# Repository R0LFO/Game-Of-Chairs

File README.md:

# Game-Of-Chairs
ECE 362 miniproject

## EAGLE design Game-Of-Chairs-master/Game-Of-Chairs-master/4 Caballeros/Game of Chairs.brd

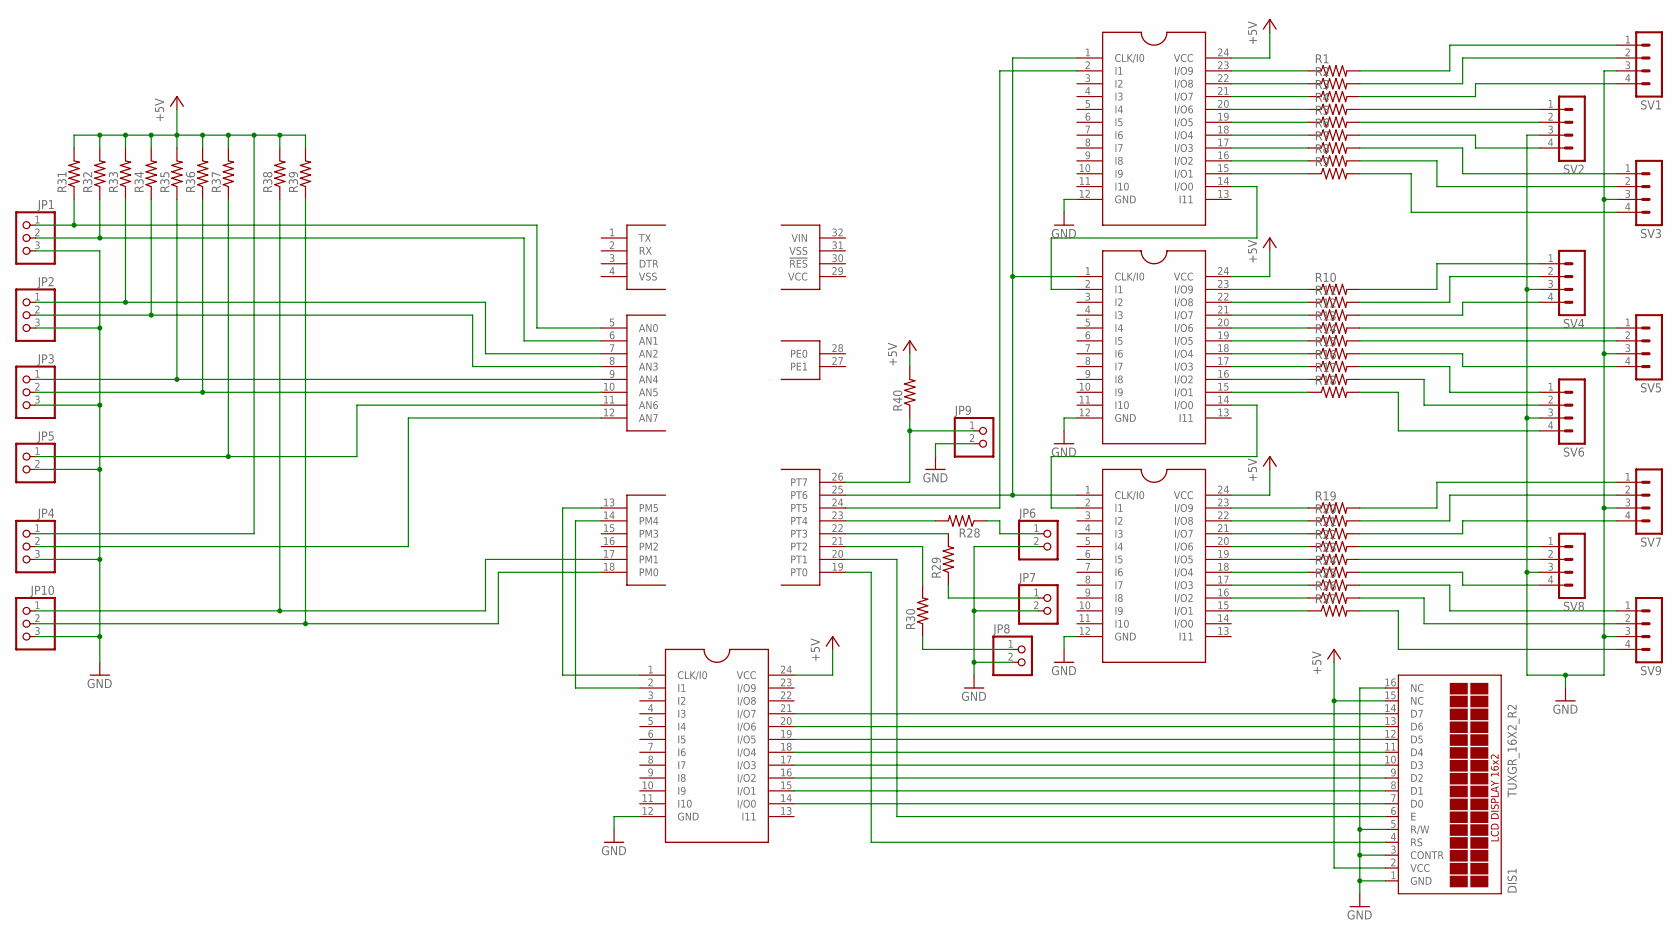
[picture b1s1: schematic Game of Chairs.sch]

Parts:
DIS1: TUXGR_16X2_R2
GAL1, GAL2, GAL3, GAL4: GAL; DIL20
JP1, JP2, JP3, JP4, JP10: PINHD-1X3; 1X03
JP5, JP6, JP7, JP8, JP9: PINHD-1X2; 1X02
R1, R2, R3, R4, R5, R6, R7, R8, R9, R10, R11, R12, R13, R14, R15, R16, R17, R18, R19, R20, R21, R22, R23, R24, R25, R26, R27, R28, R29, R30, R31, R32, R33, R34, R35, R36, R37, R38, R39, R40: R-US_0207/12; 0207/12
SV1, SV2, SV3, SV4, SV5, SV6, SV7, SV8, SV9: MA04-1
U1: 362MICRO362MICRO; 40P

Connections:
+5V: DIS1.2 (VCC), DIS1.15 (NC), GAL1.24 (VCC), GAL2.24 (VCC), GAL3.24 (VCC), GAL4.24 (VCC), JP4.1, R31.2, R32.2, R33.2, R34.2, R35.2, R36.2, R37.2, R38.2, R39.2, R40.2
GND: DIS1.1 (GND), DIS1.3 (CONTR), DIS1.5 (R/W), DIS1.16 (NC), GAL1.12 (GND), GAL2.12 (GND), GAL3.12 (GND), GAL4.12 (GND), JP1.3, JP2.3, JP3.3, JP4.3, JP5.2, JP6.2, JP7.2, JP8.2, JP9.2, JP10.3, SV1.3, SV2.3, SV3.3, SV4.3, SV5.3, SV6.3, SV7.3, SV8.3, SV9.3
unnamed: R1.2, SV1.1
unnamed: R2.2, SV1.2
unnamed: R3.2, SV1.4
unnamed: GAL1.23 (I/O9), R1.1
unnamed: GAL1.22 (I/O8), R2.1
unnamed: R6.2, SV2.4
unnamed: R7.2, SV3.1
unnamed: R8.2, SV3.2
unnamed: R9.2, SV3.4
unnamed: R10.2, SV4.1
unnamed: R11.2, SV4.2
unnamed: R12.2, SV4.4
unnamed: GAL1.21 (I/O7), R3.1
unnamed: GAL1.20 (I/O6), R4.1
unnamed: R15.2, SV5.4
unnamed: R16.2, SV6.1
unnamed: R17.2, SV6.2
unnamed: R18.2, SV6.4
unnamed: GAL1.14 (I/O0), GAL2.2 (I1)
unnamed: GAL2.14 (I/O0), GAL3.2 (I1)
unnamed: R19.2, SV7.1
unnamed: R20.2, SV7.2
unnamed: R21.2, SV7.4
unnamed: R4.2, SV2.1
unnamed: GAL1.19 (I/O5), R5.1
unnamed: R24.2, SV8.4
unnamed: R25.2, SV9.1
unnamed: R26.2, SV9.2
unnamed: R27.2, SV9.4
unnamed: GAL1.1 (CLK/I0), GAL2.1 (CLK/I0), GAL3.1 (CLK/I0), U1.25 (PT6)
unnamed: GAL1.2 (I1), U1.24 (PT5)
unnamed: GAL4.1 (CLK/I0), U1.13 (PM5)
unnamed: GAL4.2 (I1), U1.14 (PM4)
unnamed: R5.2, SV2.2
unnamed: GAL1.18 (I/O4), R6.1
unnamed: GAL1.17 (I/O3), R7.1
unnamed: GAL1.16 (I/O2), R8.1
unnamed: GAL1.15 (I/O1), R9.1
unnamed: GAL2.23 (I/O9), R10.1
unnamed: GAL2.22 (I/O8), R11.1
unnamed: GAL2.21 (I/O7), R12.1
unnamed: GAL2.20 (I/O6), R13.1
unnamed: GAL2.19 (I/O5), R14.1
unnamed: GAL2.18 (I/O4), R15.1
unnamed: GAL2.17 (I/O3), R16.1
unnamed: GAL2.16 (I/O2), R17.1
unnamed: GAL2.15 (I/O1), R18.1
unnamed: R14.2, SV5.2
unnamed: R13.2, SV5.1
unnamed: GAL3.23 (I/O9), R19.1
unnamed: GAL3.22 (I/O8), R20.1
unnamed: GAL3.21 (I/O7), R21.1
unnamed: GAL3.20 (I/O6), R22.1
unnamed: GAL3.19 (I/O5), R23.1
unnamed: GAL3.18 (I/O4), R24.1
unnamed: GAL3.17 (I/O3), R25.1
unnamed: GAL3.16 (I/O2), R26.1
unnamed: GAL3.15 (I/O1), R27.1
unnamed: R23.2, SV8.2
unnamed: R22.2, SV8.1
unnamed: JP1.1, R31.1, U1.5 (AN0)
unnamed: JP1.2, R32.1, U1.6 (AN1)
unnamed: JP2.1, R33.1, U1.7 (AN2)
unnamed: JP2.2, R34.1, U1.8 (AN3)
unnamed: JP3.1, R35.1, U1.9 (AN4)
unnamed: JP3.2, R36.1, U1.10 (AN5)
unnamed: JP5.1, R37.1, U1.11 (AN6)
unnamed: JP9.1, R40.1, U1.26 (PT7)
unnamed: JP10.1, R38.1, U1.17 (PM1)
unnamed: JP10.2, R39.1, U1.18 (PM0)
unnamed: JP4.2, U1.12 (AN7)
unnamed: R28.2, U1.23 (PT4)
unnamed: JP6.1, R28.1
unnamed: R29.2, U1.22 (PT3)
unnamed: R30.2, U1.21 (PT2)
unnamed: JP7.1, R29.1
unnamed: JP8.1, R30.1
unnamed: DIS1.6 (E), U1.20 (PT1)
unnamed: DIS1.4 (RS), U1.19 (PT0)
unnamed: DIS1.7 (D0), GAL4.14 (I/O0)
unnamed: DIS1.8 (D1), GAL4.15 (I/O1)
unnamed: DIS1.9 (D2), GAL4.16 (I/O2)
unnamed: DIS1.10 (D3), GAL4.17 (I/O3)
unnamed: DIS1.11 (D4), GAL4.18 (I/O4)
unnamed: DIS1.12 (D5), GAL4.19 (I/O5)
unnamed: DIS1.13 (D6), GAL4.20 (I/O6)
unnamed: DIS1.14 (D7), GAL4.21 (I/O7)

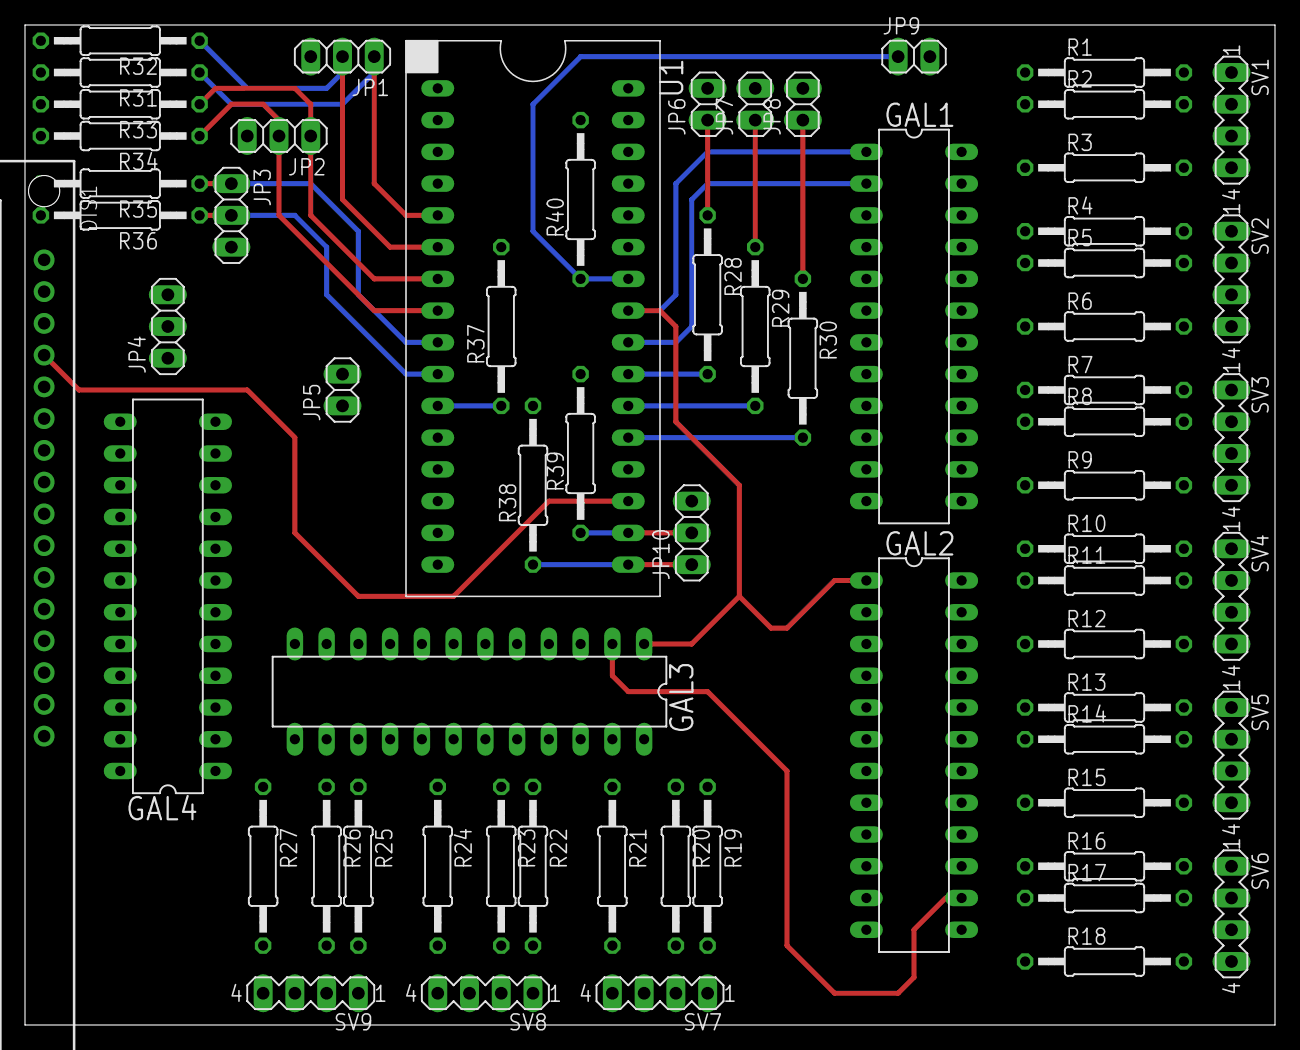
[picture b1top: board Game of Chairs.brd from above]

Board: 2 copper layers, 100.0 x 80.0 mm, 65 parts (0 on the bottom side), 89 nets.

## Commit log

2016-11-19 Shematic and libraries for project
2016-11-19 PCB layout V1
